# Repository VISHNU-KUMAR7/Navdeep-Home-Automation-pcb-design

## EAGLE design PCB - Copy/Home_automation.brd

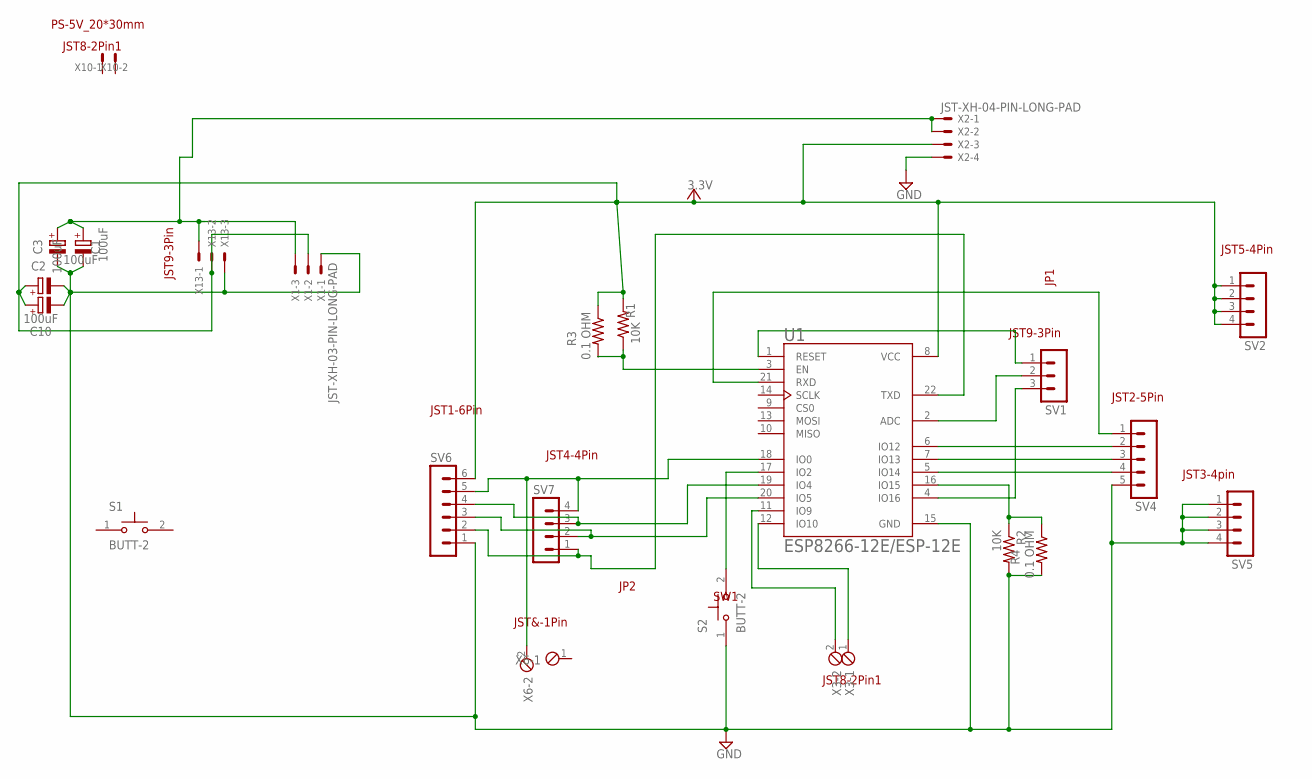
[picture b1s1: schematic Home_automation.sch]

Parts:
C1, C10: 100uF; SMC_B
C2, C3: 100uF; E2,5-6E
R1, R2: 10K; R0805
R3, R4: 0.1 OHM; 0207/10
S1, S2: BUTT-2; SW_BUTT-2
SV1: MA03-1
SV2, SV5, SV7: MA04-1
SV4: MA05-1
SV6: MA06-1
U1: ESP8266-12E/ESP-12E; XCVR_ESP8266-12E/ESP-12E
X1: JST-XH-03-PIN-LONG-PAD; JST-XH-03-PACKAGE-LONG-PAD
X2: JST-XH-04-PIN-LONG-PAD; JST-XH-04-PACKAGE-LONG-PAD
X3, X6: MPT2; 2POL254
X10: JST-XH-02-PIN-LONG-PAD; JST-XH-02-PACKAGE-LONG-PAD
X13: JST9-3Pin; JST-XH-03-PACKAGE-LONG-PAD

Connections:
GND: C1.-, C2.-, C3.-, C10.-, R2.2, R4.2, S2.1, SV4.5, SV5.1, SV5.2, SV5.3, SV5.4, SV6.1, U1.15 (GND), X1.1, X2.4, X13.3
unnamed: SV4.3, U1.7 (IO13)
unnamed: SV4.2, U1.6 (IO12)
unnamed: SV4.4, U1.5 (IO14)
unnamed: SV4.1, U1.21 (RXD)
unnamed: R1.1, R3.2, U1.3 (EN)
unnamed: SV6.2, SV7.1, U1.22 (TXD)
unnamed: C1.+, C3.+, X1.3, X2.1, X2.2, X13.1
unnamed: SV6.3, SV7.2, U1.20 (IO5)
unnamed: SV6.4, SV7.3, U1.19 (IO4)
unnamed: SV6.5, SV7.4, U1.18 (IO0), X6.2
unnamed: R2.1, R4.1, U1.16 (IO15)
unnamed: S2.2, U1.17 (IO2)
unnamed: U1.12 (IO10), X3.1
unnamed: U1.11 (IO9), X3.2
unnamed: SV1.1, U1.1 (RESET)
unnamed: SV1.2, U1.2 (ADC)
unnamed: SV1.3, U1.4 (IO16)
VCC: C2.+, C10.+, R1.2, R3.1, SV2.1, SV2.2, SV2.3, SV2.4, SV6.6, U1.8 (VCC), X1.2, X2.3, X13.2

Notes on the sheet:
JP1
JP2
JST1-6Pin
JST4-4Pin
JST3-4pin
JST2-5Pin
JST5-4Pin
SW1
JST&-1Pin
JST8-2Pin1
JST9-3Pin
PS-5V_20*30mm

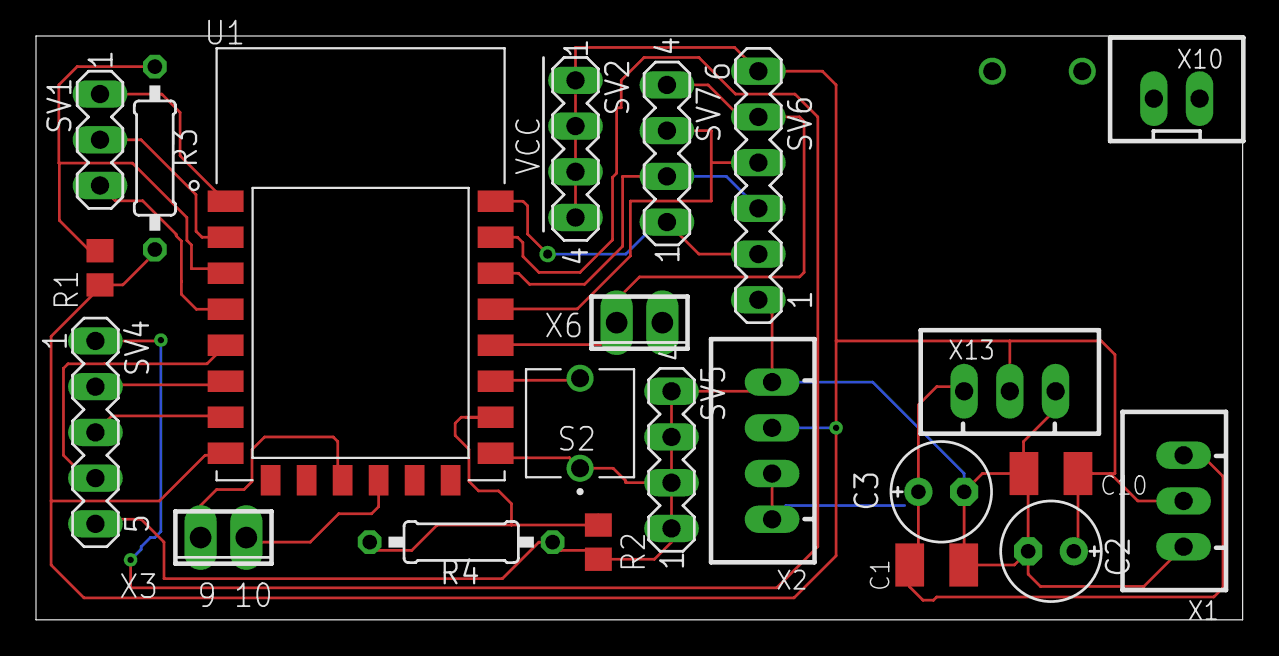
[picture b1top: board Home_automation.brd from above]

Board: 2 copper layers, 67.0 x 32.4 mm, 23 parts (0 on the bottom side), 19 nets.

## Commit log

2021-04-21 Main PCB that is original PCB
